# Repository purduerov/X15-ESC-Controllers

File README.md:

# Readme for X15-ESC-Controllers

Whenever you make a new part, download the datasheet and save it here _**and**_ with the part in the parts library

Always pull other people's changes before beginning to work
`git pull`

Be sure to push your changes after  working on them. Run:
1. `git add .` to add any files in this directory or a subdirectory
or `git add -u` to add any modified files
2. (Optional) `git clean -nX` to see what ignored files can be removed
	`git clean -fX` removes ignored files (Eagle backups)
3. `git commit -m "helpful commit message"` with a description of the work that you did
4. `git push` to push your work to github

Other helpful commands
* `git status` says information about modified and staged files
* `git log` shows the recent commits of the repository
* `git log filename.extension` show the recent commits for just that file
* `git checkout first-couple-letter-of-commit-id` lets you go back to a previous version
* `git checkout master` brings you back to the latest commit
* `git tag` lists the tags
* `git tag -a orderX -m "the version of the board placed for the X'th order"` tag a specific commit
* `git push --tags` needed to push tags to remote
* `git show orderX` show the commit log for the given tag
* `git checkout orderX` go back and interact with the files at the tagged commit

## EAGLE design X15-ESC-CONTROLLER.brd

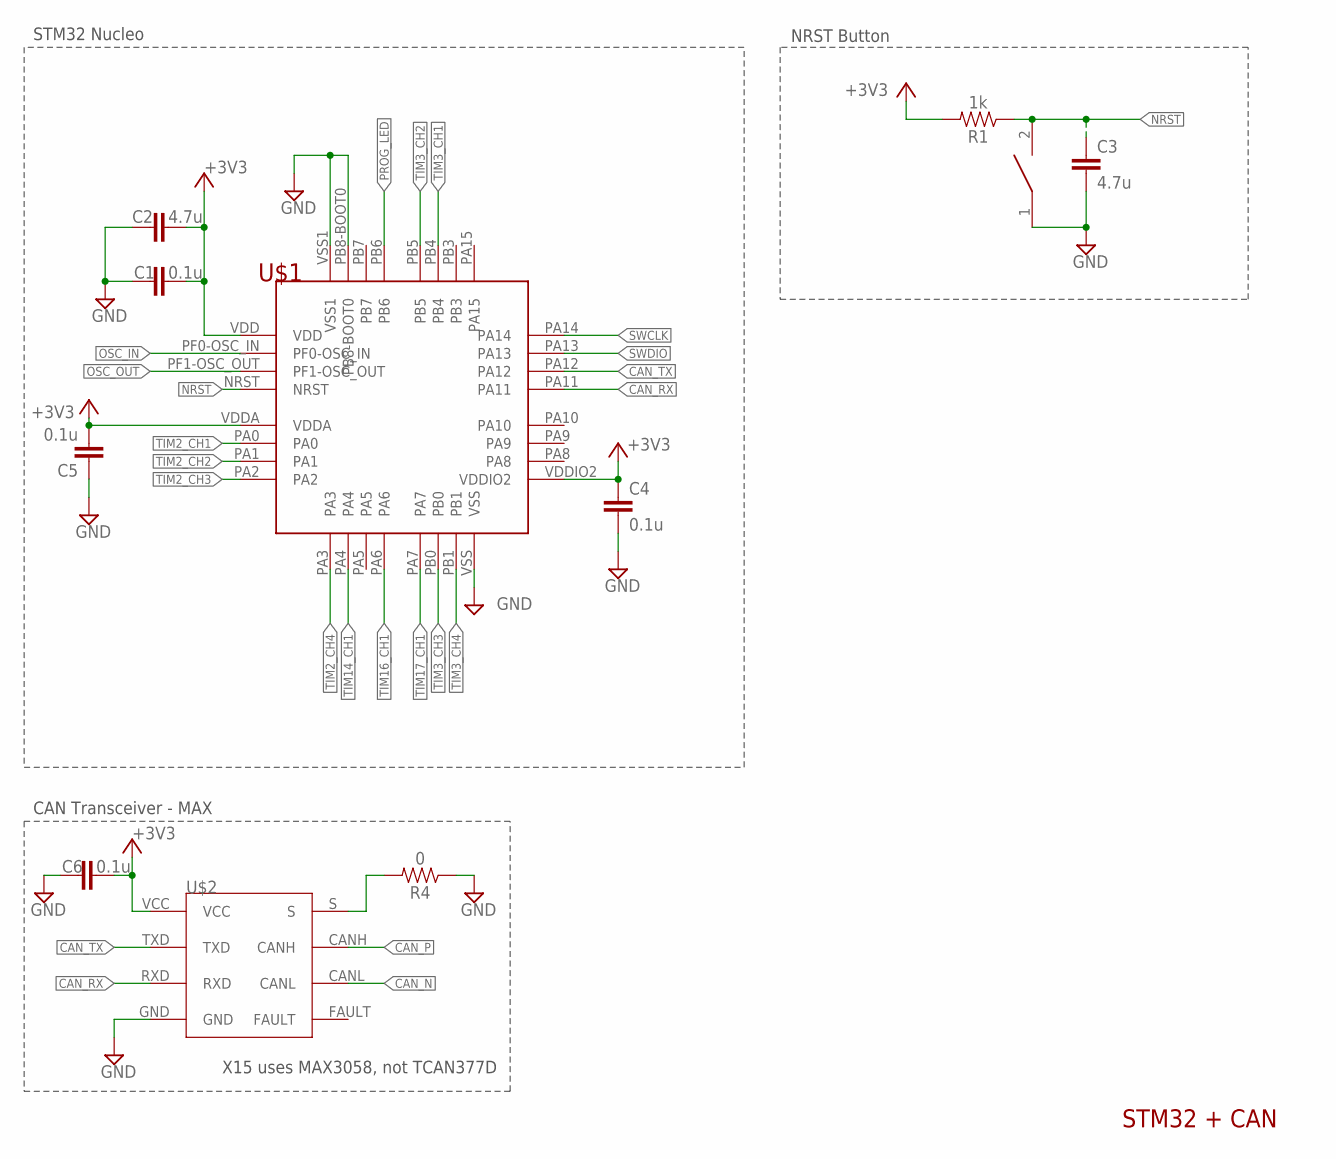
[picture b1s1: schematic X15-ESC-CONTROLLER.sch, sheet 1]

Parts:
C1, C4, C5, C6: 0.1u; 0603
C2, C3: 4.7u; 0603
R1: 1k; 0603
R4: 0; 0603
U$1: STM32F042K6T6
U$2: TCAN337D
U$7: DISCRETECOMPONENTS_SWITCH; DISCRETECOMPONENTS_SW_2512

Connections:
+3V3: C1.1, C2.2, C4.1, C5.1, C6.2, R1.2, U$1.VDD, U$1.VDDA, U$1.VDDIO2, U$2.VCC; also elsewhere on the board
CAN_N: U$2.CANL; also elsewhere on the board
CAN_P: U$2.CANH; also elsewhere on the board
CAN_RX: U$1.PA11, U$2.RXD
CAN_TX: U$1.PA12, U$2.TXD
GND: C1.2, C2.1, C3.2, C4.2, C5.2, C6.1, R4.1, U$1.PB8-BOOT0, U$1.VSS, U$1.VSS1, U$2.GND, U$7.1; also elsewhere on the board
unnamed: R4.2, U$2.S
NRST: C3.1, R1.1, U$1.NRST, U$7.2; also elsewhere on the board
OSC_IN: U$1.PF0-OSC_IN
OSC_OUT: U$1.PF1-OSC_OUT
PROG_LED: U$1.PB6; also elsewhere on the board
SWCLK: U$1.PA14; also elsewhere on the board
SWDIO: U$1.PA13; also elsewhere on the board
TIM2_CH1: U$1.PA0; also elsewhere on the board
TIM2_CH2: U$1.PA1; also elsewhere on the board
TIM2_CH3: U$1.PA2; also elsewhere on the board
TIM2_CH4: U$1.PA3; also elsewhere on the board
TIM3_CH1: U$1.PB4; also elsewhere on the board
TIM3_CH2: U$1.PB5; also elsewhere on the board
TIM3_CH3: U$1.PB0; also elsewhere on the board
TIM3_CH4: U$1.PB1; also elsewhere on the board
TIM14_CH1: U$1.PA4; also elsewhere on the board
TIM16_CH1: U$1.PA6; also elsewhere on the board
TIM17_CH1: U$1.PA7; also elsewhere on the board

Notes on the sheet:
CAN Transceiver - MAX
NRST Button
STM32 + CAN
STM32 Nucleo
X15 uses MAX3058, not TCAN377D

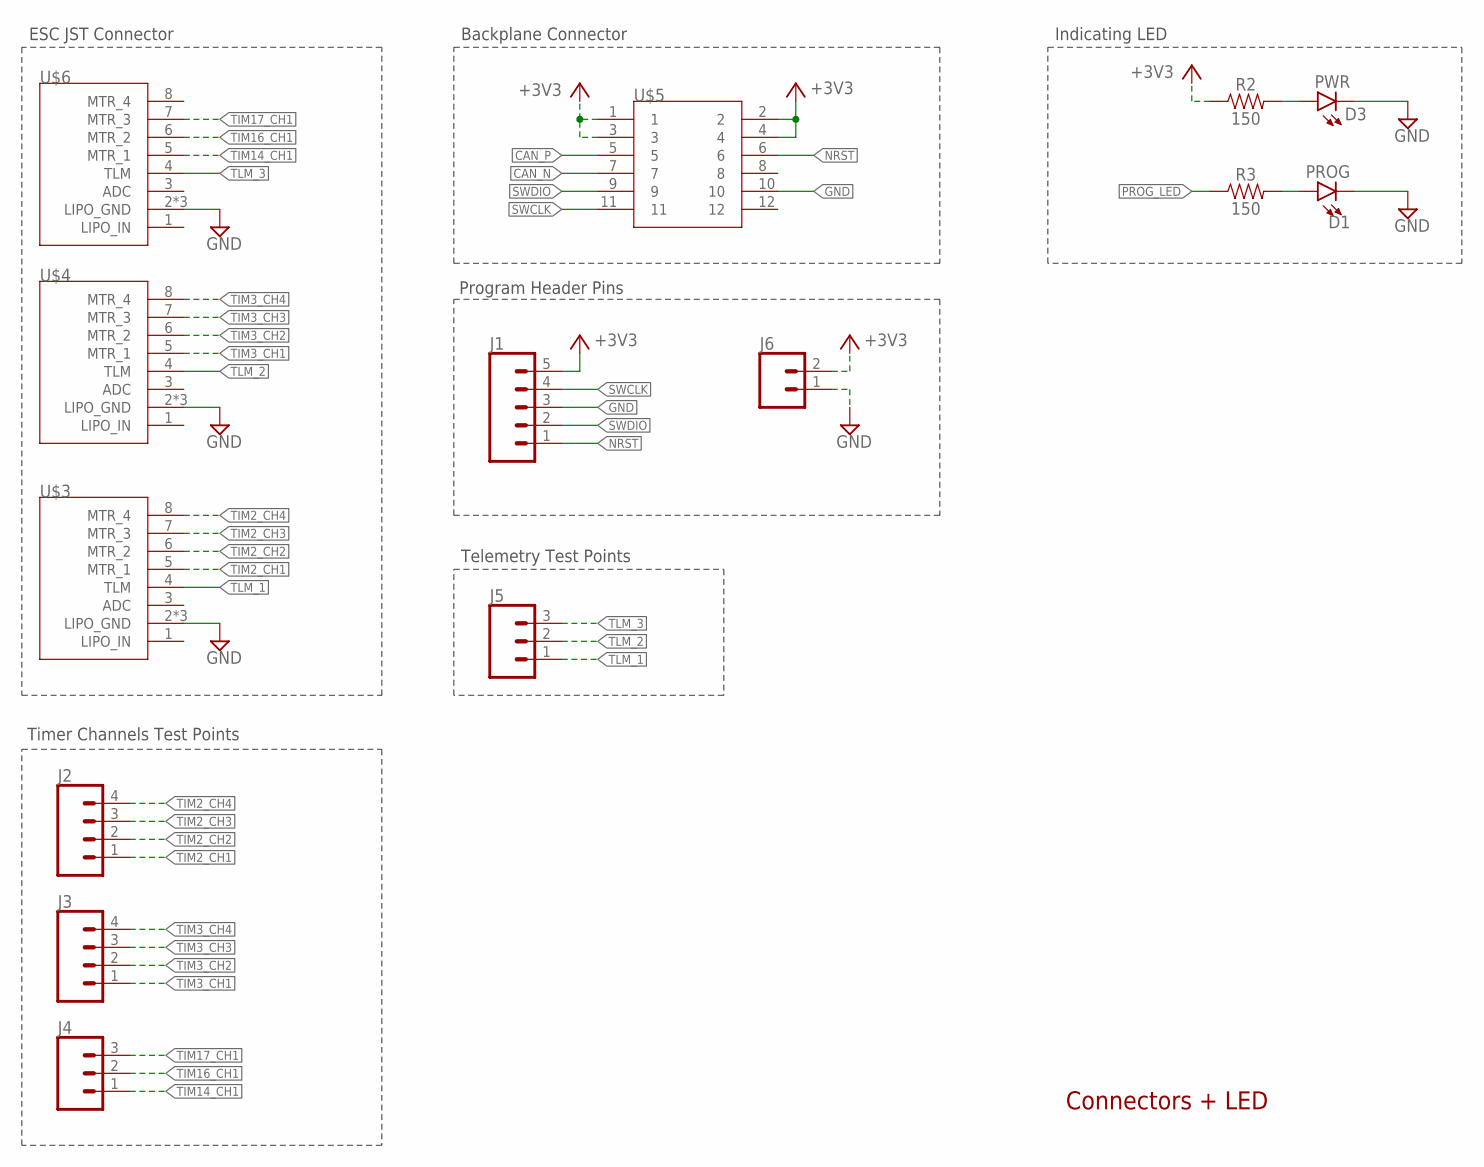
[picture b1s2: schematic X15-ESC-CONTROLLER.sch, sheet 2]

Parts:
D1: PROG; 0805
D3: PWR; 0805
J1: CONN_05; 1X05
J2, J3: CONN_04; 1X04
J4, J5: CONN_03; 1X03
J6: CONN_02; 1X02
R2, R3: 150; 0603
U$3, U$4, U$6: JST_8_PIN; 8PIN_CONNECTOR
U$5: BAKCPLANE_CONNECTOR; BACKPLANE_CONNECTORS_BKP

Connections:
+3V3: J1.5, J6.2, R2.1, U$5.1, U$5.2, U$5.3, U$5.4; also elsewhere on the board
CAN_N: U$5.7; also elsewhere on the board
CAN_P: U$5.5; also elsewhere on the board
GND: D1.C, D3.C, J1.3, J6.1, U$3.2 (LIPO_GND), U$3.MECH1 (LIPO_GND), U$3.MECH2 (LIPO_GND), U$4.2 (LIPO_GND), U$4.MECH1 (LIPO_GND), U$4.MECH2 (LIPO_GND), U$5.10, U$6.2 (LIPO_GND), U$6.MECH1 (LIPO_GND), U$6.MECH2 (LIPO_GND); also elsewhere on the board
unnamed: D3.A, R2.2
unnamed: D1.A, R3.2
NRST: J1.1, U$5.6; also elsewhere on the board
PROG_LED: R3.1; also elsewhere on the board
SWCLK: J1.4, U$5.11; also elsewhere on the board
SWDIO: J1.2, U$5.9; also elsewhere on the board
TIM2_CH1: J2.1, U$3.5 (MTR_1); also elsewhere on the board
TIM2_CH2: J2.2, U$3.6 (MTR_2); also elsewhere on the board
TIM2_CH3: J2.3, U$3.7 (MTR_3); also elsewhere on the board
TIM2_CH4: J2.4, U$3.8 (MTR_4); also elsewhere on the board
TIM3_CH1: J3.1, U$4.5 (MTR_1); also elsewhere on the board
TIM3_CH2: J3.2, U$4.6 (MTR_2); also elsewhere on the board
TIM3_CH3: J3.3, U$4.7 (MTR_3); also elsewhere on the board
TIM3_CH4: J3.4, U$4.8 (MTR_4); also elsewhere on the board
TIM14_CH1: J4.1, U$6.5 (MTR_1); also elsewhere on the board
TIM16_CH1: J4.2, U$6.6 (MTR_2); also elsewhere on the board
TIM17_CH1: J4.3, U$6.7 (MTR_3); also elsewhere on the board
TLM_1: J5.1, U$3.4 (TLM)
TLM_2: J5.2, U$4.4 (TLM)
TLM_3: J5.3, U$6.4 (TLM)

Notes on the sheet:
ESC JST Connector
Timer Channels Test Points
Backplane Connector
Program Header Pins
Indicating LED
Connectors + LED
Telemetry Test Points

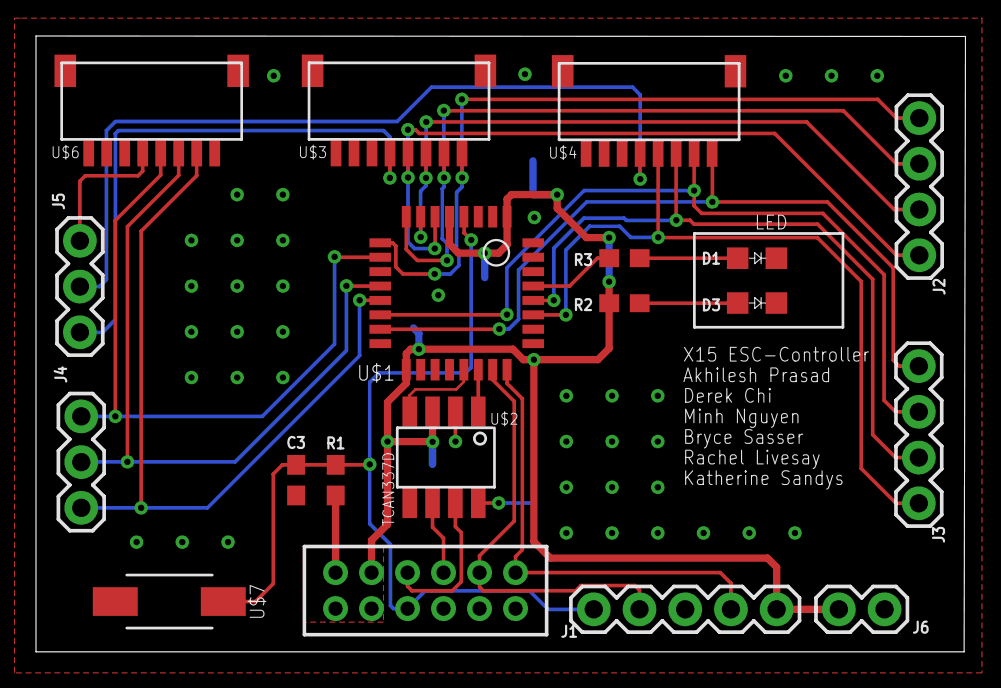
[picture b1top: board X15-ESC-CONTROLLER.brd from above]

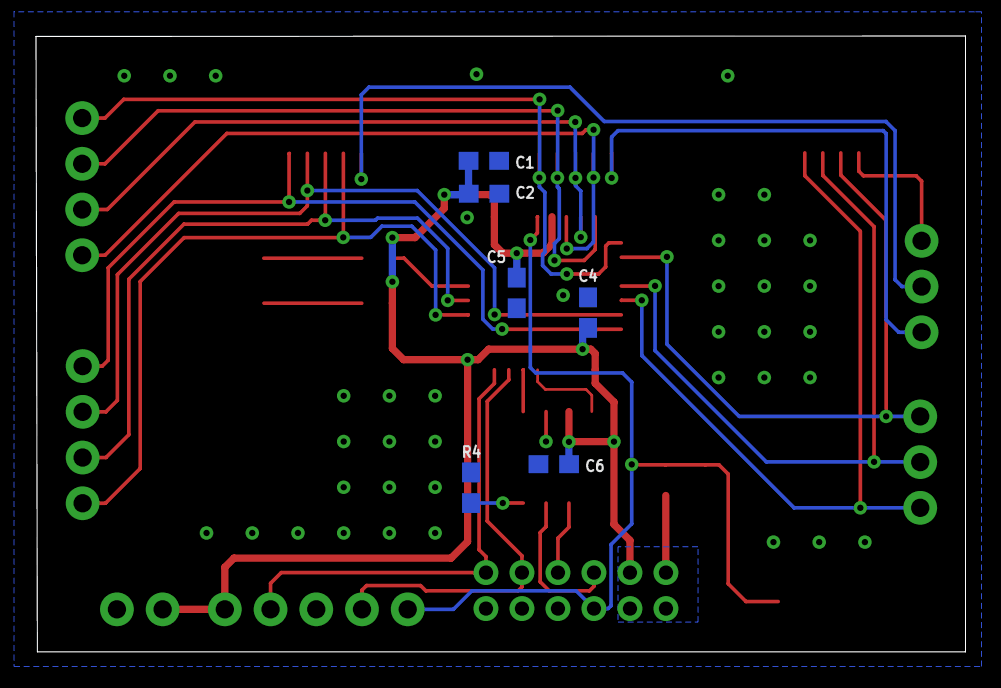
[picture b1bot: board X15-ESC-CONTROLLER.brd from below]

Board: 2 copper layers, 51.6 x 34.2 mm, 25 parts (6 on the bottom side), 27 nets.

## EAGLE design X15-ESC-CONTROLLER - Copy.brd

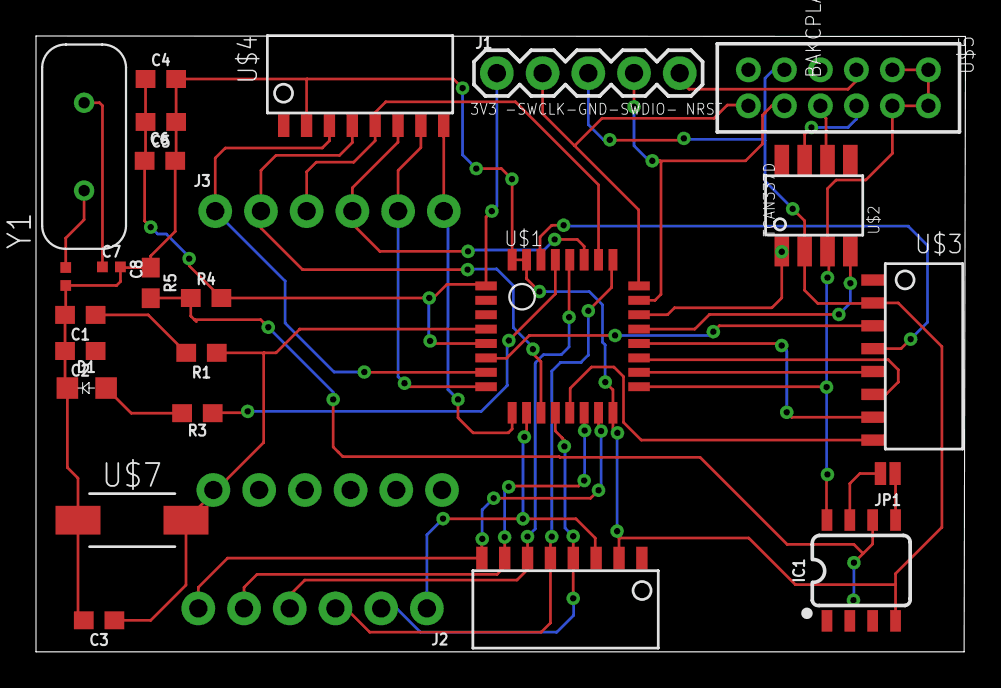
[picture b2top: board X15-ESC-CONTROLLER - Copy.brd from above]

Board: 2 copper layers, 51.6 x 34.2 mm, 27 parts (1 on the bottom side), 35 nets.

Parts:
C1, C4, C5, C6: 0.1uF; 0603
C2, C3: 4.7uF; 0603
C7, C8: 20pF; 0402-TIGHT
D1: COLOR; 0805
IC1: OP-AMP; SO08
J1: 3V3 -SWCLK-GND-SWDIO- NRST; 1X05
J2, J3, J4: 1X06_NO_SILK
JP1: JUMPER-SMT_2_NO_NO-SILK; SMT-JUMPER_2_NO_NO-SILK
R1, R4: 1k; 0603
R3: 470; 0603
R5: 3.3k; 0603
U$1: STM32F042K6T6
U$2: TCAN337D
U$3, U$4, U$6: JST_8_PIN
U$5: BAKCPLANE_CONNECTOR; BACKPLANE_CONNECTORS_BKP
U$7: DISCRETECOMPONENTS_SW_2512
Y1: ECS-80-S-4X; XTAL_ECS-80-S-4X

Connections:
+3V3: C1.1, C2.1, C4.1, C5.2, C6.1, IC1.8, J1.1, R1.2, R4.2, U$1.VDD, U$1.VDDA, U$1.VDDIO2, U$2.VCC, U$5.1, U$5.2, U$5.3, U$5.4
ADC_IN0: J4.1, U$1.PA0, U$3.3
ADC_IN1: J3.1, U$1.PA1, U$4.3
ADC_IN4: J2.1, U$1.PA4, U$6.3
CAN_H: U$2.CANH, U$5.5
CAN_L: U$2.CANL, U$5.7
CAN_RX: U$1.PA11, U$2.RXD
CAN_TX: U$1.PA12, U$2.TXD
GND: C1.2, C2.2, C3.2, C4.2, C5.1, C6.2, C7.2, C8.2, D1.C, IC1.4, J1.3, R5.1, U$1.PB8-BOOT0, U$1.VSS, U$1.VSS1, U$2.GND, U$3.2, U$4.2, U$5.10, U$6.2, U$7.1
unnamed: C3.1, R1.1, U$1.NRST, U$7.2
unnamed: IC1.6, R4.1, R5.2
unnamed: R3.1, U$1.PB6
unnamed: C7.1, Y1.2
unnamed: C8.1, Y1.1
unnamed: D1.A, R3.2
NRST: J1.5, U$5.6
SWCLK: J1.2, U$1.PA14, U$5.11
SWDIO: J1.4, U$1.PA13, U$5.9
TIM1_CH1: J4.3, U$1.PA8, U$3.5
TIM1_CH2: U$1.PA9, U$3.6
TIM1_CH3: J4.5, U$1.PA10, U$3.7
TIM2_CH1: J3.3, U$1.PB3, U$4.5
TIM2_CH2: J3.4, J4.4, U$1.PB4, U$4.6
TIM2_CH3: J3.5, U$1.PA2, U$4.7
TIM2_CH4: J3.6, U$1.PA3, U$4.8
TIM3_CH2: J2.4, U$1.PB5, U$6.6
TIM3_CH3: J2.5, U$1.PB0, U$6.7
TIM3_CH4: J2.6, U$1.PB1, U$6.8
TIM16_CH1: J2.3, U$1.PA15, U$6.5
TIM17_CH1: J4.6, U$1.PA7, U$3.8
TLM: IC1.7, JP1.2
TLM_1: J4.2, U$1.PB7, U$3.4
TLM_2: J3.2, U$1.PA5, U$4.4
TLM_3: J2.2, U$1.PA6, U$6.4
TLM_ESC: IC1.5, JP1.1

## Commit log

2022-10-01 Second Attempt to Push
2022-10-12 Update 2 Trial Again
2022-10-15 Design Review Push
2022-10-27 3rd Esc added
2022-10-29 Fixed board and schematic communication issue
2022-10-29 Fixed board and schematic communication issue for real this time
2022-11-03 Board dimensions
2022-11-07 Board Edits
2022-11-10 Intermediate Board
2022-11-11 Board Traces Completed
2022-11-11 FIxed DRC
2022-11-19 Test
2022-12-01 Almost Finished Rewiring
    Look at the copy
2022-12-03 broken
2022-12-03 Final Board Edits
2022-12-03 almost done
2022-12-03 First finished version
2022-12-10 Final Version 2
2022-12-22 Update Parts Library
2022-12-22 Fix some traces with polygons
2022-12-22 Add 3.3V testing LED
2022-12-22 Update .brd file
2022-12-27 Complete Board
2023-01-02 Fix .brd files
2023-01-12 Hopeful Final Push
2023-04-24 Design X15 ESC Controller Again
2023-04-25 Fix New Version of X15-ESC Controller
2023-04-25 Complete New Version of X15 ESC Controller Board
2023-04-25 Minor Change

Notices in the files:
parts and their libraries:
SparkFun-Capacitors: Licensing: Creative Commons ShareAlike 4.0 International - https://creativecommons.org/licenses/by-sa/4.0
